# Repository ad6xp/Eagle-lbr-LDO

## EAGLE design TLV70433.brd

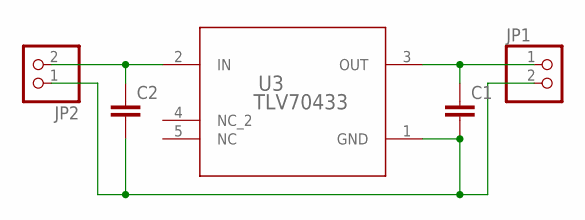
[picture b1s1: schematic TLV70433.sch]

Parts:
C1, C2: C-EUC1206; C1206
JP1, JP2: PINHD-1X2; 1X02
U3: TLV70433; DBV0005A_N

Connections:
GND: C1.2, C2.2, JP1.2, JP2.1, U3.1 (GND)
VIN: C2.1, JP2.2, U3.2 (IN)
VOUT: C1.1, JP1.1, U3.3 (OUT)

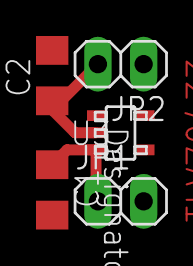
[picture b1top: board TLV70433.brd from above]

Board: 2 copper layers, 5 parts (0 on the bottom side), 3 nets.

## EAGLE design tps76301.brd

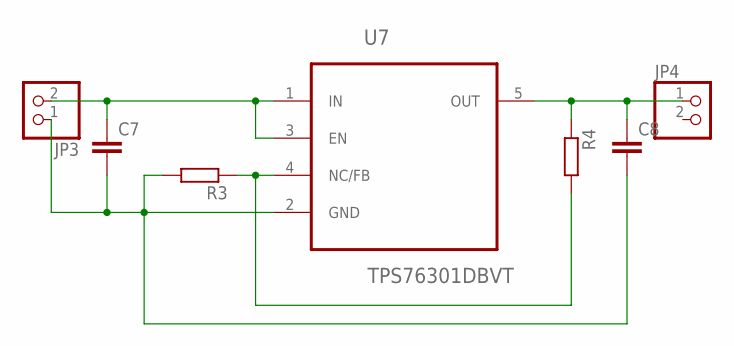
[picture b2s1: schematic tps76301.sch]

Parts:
C7, C8: C-EUC0805; C0805
JP3, JP4: PINHD-1X2; 1X02
R3, R4: R-EU_R0805; R0805
U7: TPS76301DBVT; SOT95P280X145-5N

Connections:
GND: C7.2, C8.2, JP3.1, R3.2, U7.2 (GND)
unnamed: R3.1, R4.2, U7.4 (NC/FB)
unnamed: C8.1, JP4.1, R4.1, U7.5 (OUT)
unnamed: C7.1, JP3.2, U7.1 (IN), U7.3 (EN)

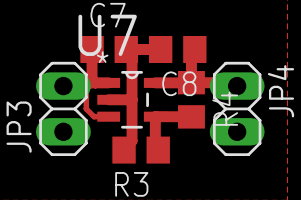
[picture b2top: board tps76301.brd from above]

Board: 2 copper layers, 7 parts (0 on the bottom side), 4 nets.

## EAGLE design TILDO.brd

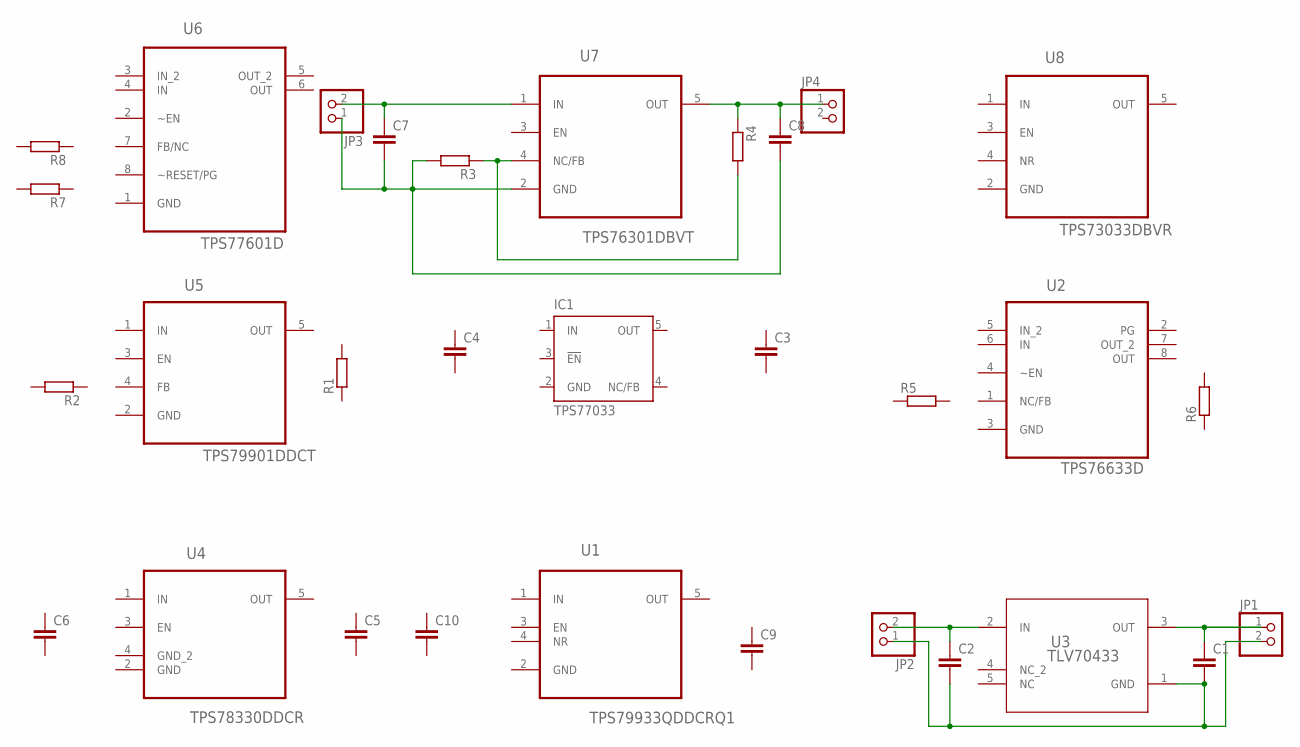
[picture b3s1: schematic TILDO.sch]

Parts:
C1, C2, C3, C4, C9, C10: C-EUC1206; C1206
C5, C6, C7, C8: C-EUC0805; C0805
IC1: TPS77033; SOT23-DBV
JP1, JP2, JP3, JP4: PINHD-1X2; 1X02
R1, R2, R3, R4, R5, R6, R7, R8: R-EU_R0805; R0805
U1: TPS79933QDDCRQ1; SOT95P280X110-5N
U2: TPS76633D; SOIC127P600X175-8N
U3: TLV70433; DBV0005A_N
U4: TPS78330DDCR; SOT95P280X110-5N
U5: TPS79901DDCT; SOT95P280X110-5N
U6: TPS77601D; SOIC127P600X175-8N
U7: TPS76301DBVT; SOT95P280X145-5N
U8: TPS73033DBVR; SOT95P280X145-5N

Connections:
GND: C1.2, C2.2, IC1.2 (GND), JP1.2, JP2.1, U3.1 (GND)
IN: U1.1 (IN), U5.1 (IN), U8.1 (IN)
unnamed: C2.1, JP2.2, U3.2 (IN)
unnamed: R3.1, R4.2, U7.4 (NC/FB)
unnamed: C1.1, JP1.1, U3.3 (OUT)
unnamed: C8.1, JP4.1, R4.1, U7.5 (OUT)
unnamed: C7.1, JP3.2, U7.1 (IN)
unnamed: C7.2, C8.2, JP3.1, R3.2, U7.2 (GND)

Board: 2 copper layers, 31 parts (0 on the bottom side), 8 nets, no tracks yet.

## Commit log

2016-04-12 Added files via upload
